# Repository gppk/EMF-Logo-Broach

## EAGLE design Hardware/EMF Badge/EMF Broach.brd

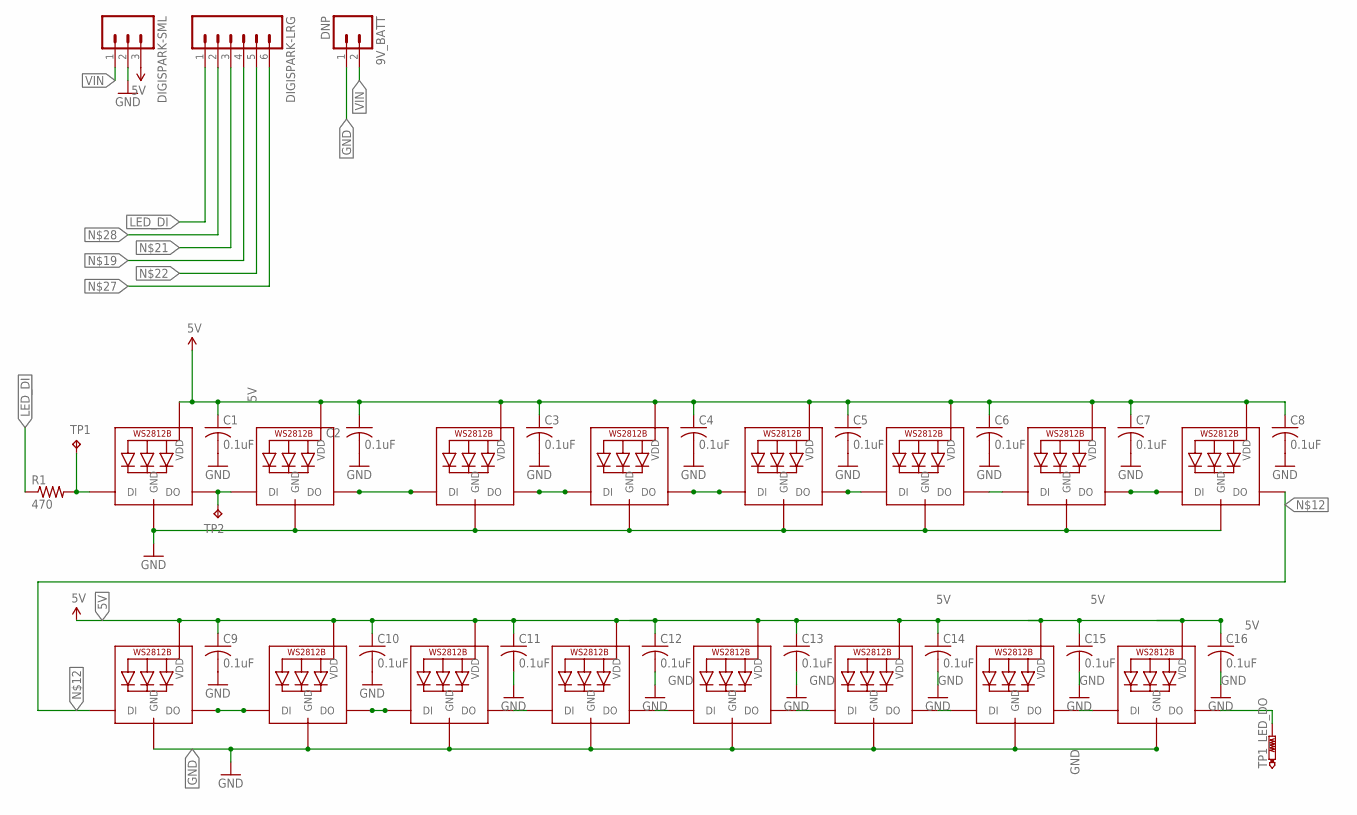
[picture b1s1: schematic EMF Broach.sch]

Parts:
9V_BATT: DNP; 02P
C1, C2, C3, C4, C5, C6, C7, C8, C9, C10, C11, C12, C13, C14, C15, C16: 0.1uF; C0603
DIGISPARK-LRG: M06SIP; 1X06
DIGISPARK-SML: M03PTH; 1X03
NEO_1, NEO_2, NEO_3, NEO_4, NEO_5, NEO_6, NEO_7, NEO_8, NEO_9, NEO_10, NEO_11, NEO_12, NEO_13, NEO_14, NEO_15, NEO_16: WS2812B5050; WS2812B
R1: 470; R0603
TP1, TP2: TPB1,27; B1,27
TP1_LED_DO: PTR1PAD1-17; P1-17

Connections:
5V: C1.1, C2.1, C3.1, C4.1, C5.1, C6.1, C7.1, C8.1, C9.1, C10.1, C11.1, C12.1, C13.1, C14.1, C15.1, C16.1, DIGISPARK-SML.3, NEO_1.1-VDD (VDD), NEO_2.1-VDD (VDD), NEO_3.1-VDD (VDD), NEO_4.1-VDD (VDD), NEO_5.1-VDD (VDD), NEO_6.1-VDD (VDD), NEO_7.1-VDD (VDD), NEO_8.1-VDD (VDD), NEO_9.1-VDD (VDD), NEO_10.1-VDD (VDD), NEO_11.1-VDD (VDD), NEO_12.1-VDD (VDD), NEO_13.1-VDD (VDD), NEO_14.1-VDD (VDD), NEO_15.1-VDD (VDD), NEO_16.1-VDD (VDD)
GND: 9V_BATT.1, C1.2, C2.2, C3.2, C4.2, C5.2, C6.2, C7.2, C8.2, C9.2, C10.2, C11.2, C12.2, C13.2, C14.2, C15.2, C16.2, DIGISPARK-SML.2, NEO_1.3-GND (GND), NEO_2.3-GND (GND), NEO_3.3-GND (GND), NEO_4.3-GND (GND), NEO_5.3-GND (GND), NEO_6.3-GND (GND), NEO_7.3-GND (GND), NEO_8.3-GND (GND), NEO_9.3-GND (GND), NEO_10.3-GND (GND), NEO_11.3-GND (GND), NEO_12.3-GND (GND), NEO_13.3-GND (GND), NEO_14.3-GND (GND), NEO_15.3-GND (GND), NEO_16.3-GND (GND)
LED_DI: DIGISPARK-LRG.1, R1.1
unnamed: NEO_1.2-DOUT (DO), NEO_2.4-DIN (DI), TP2.TP
unnamed: NEO_2.2-DOUT (DO), NEO_3.4-DIN (DI)
unnamed: NEO_10.2-DOUT (DO), NEO_11.4-DIN (DI)
unnamed: NEO_6.2-DOUT (DO), NEO_7.4-DIN (DI)
unnamed: NEO_7.2-DOUT (DO), NEO_8.4-DIN (DI)
unnamed: NEO_1.4-DIN (DI), R1.2, TP1.TP
unnamed: NEO_3.2-DOUT (DO), NEO_4.4-DIN (DI)
unnamed: NEO_4.2-DOUT (DO), NEO_5.4-DIN (DI)
unnamed: NEO_5.2-DOUT (DO), NEO_6.4-DIN (DI)
unnamed: NEO_8.2-DOUT (DO), NEO_9.4-DIN (DI)
unnamed: NEO_11.2-DOUT (DO), NEO_12.4-DIN (DI)
unnamed: NEO_9.2-DOUT (DO), NEO_10.4-DIN (DI)
unnamed: NEO_13.2-DOUT (DO), NEO_14.4-DIN (DI)
unnamed: NEO_15.2-DOUT (DO), NEO_16.4-DIN (DI)
unnamed: NEO_14.2-DOUT (DO), NEO_15.4-DIN (DI)
unnamed: NEO_12.2-DOUT (DO), NEO_13.4-DIN (DI)
unnamed: NEO_16.2-DOUT (DO), TP1_LED_DO.TP
VIN: 9V_BATT.2, DIGISPARK-SML.1

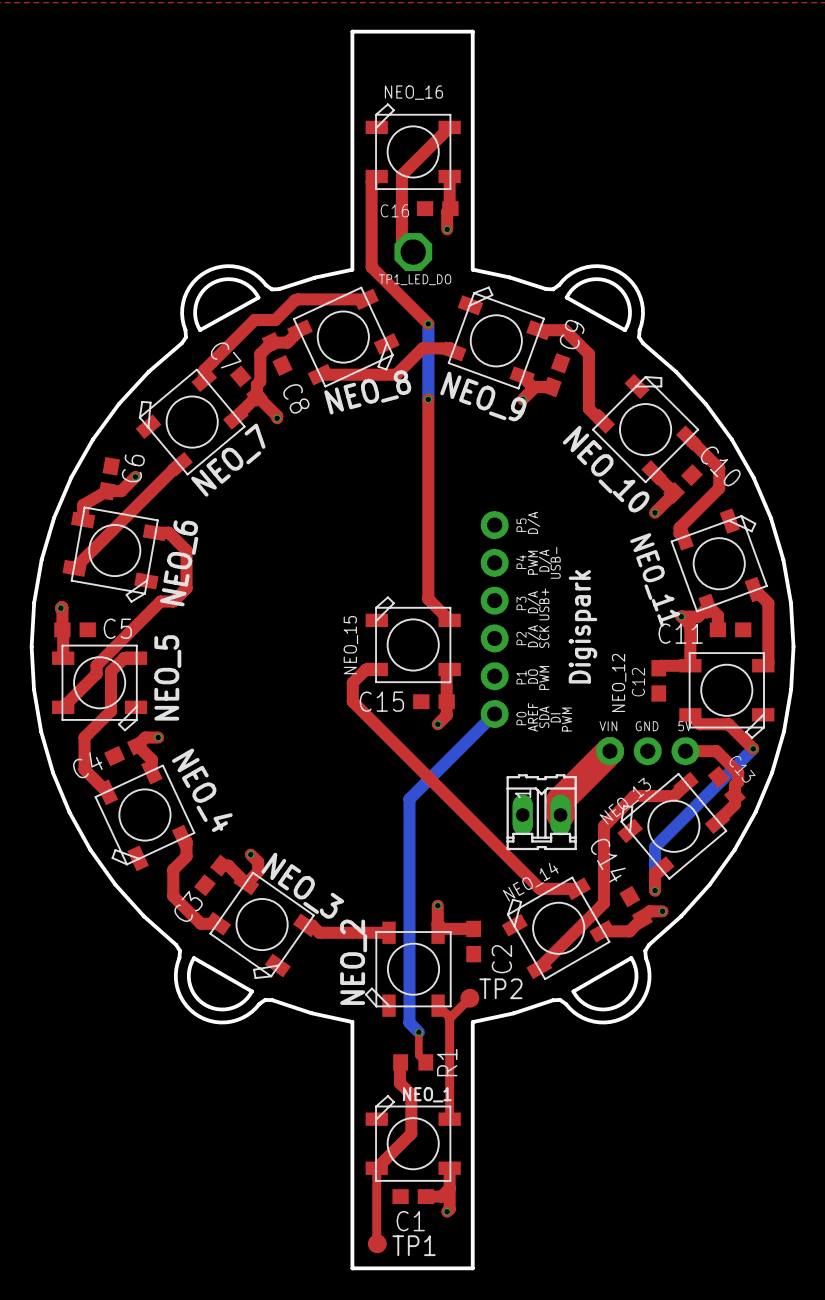
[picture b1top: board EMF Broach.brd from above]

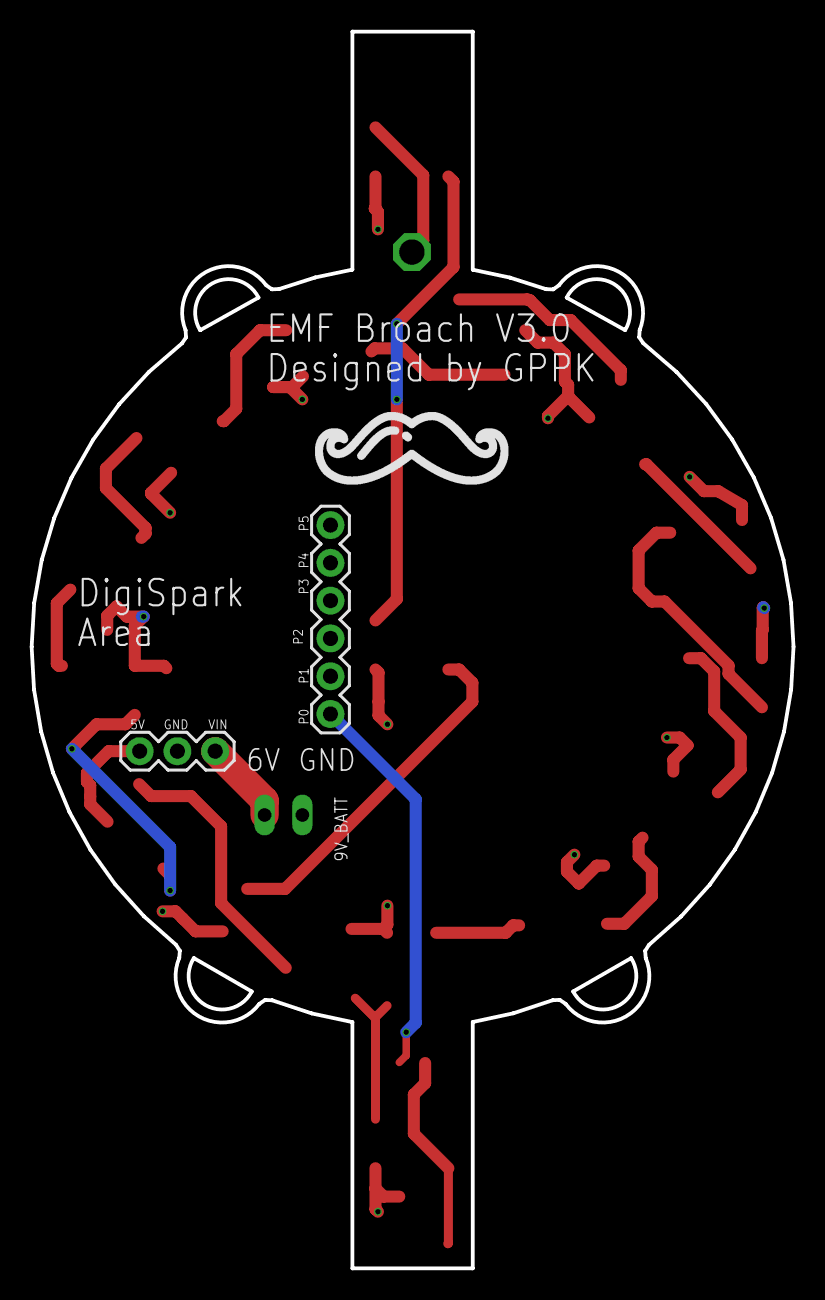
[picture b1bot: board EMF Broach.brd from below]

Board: 2 copper layers, 51.2 x 83.1 mm, 39 parts (2 on the bottom side), 21 nets.

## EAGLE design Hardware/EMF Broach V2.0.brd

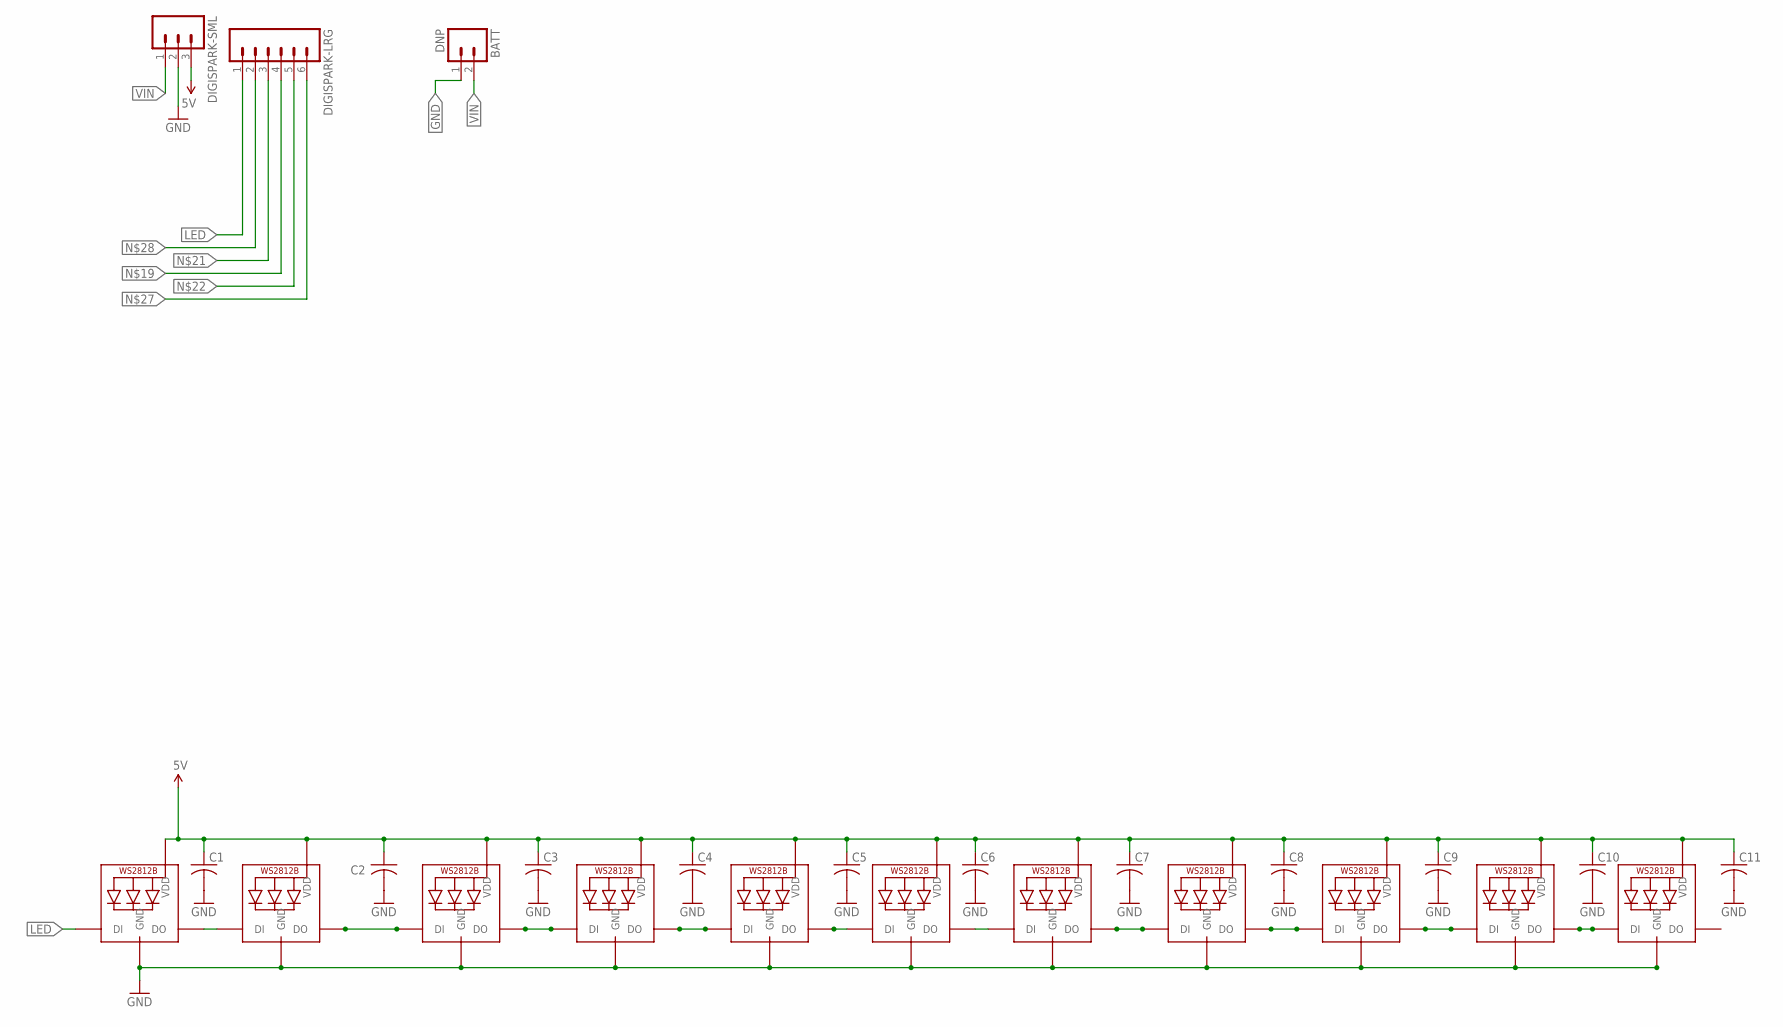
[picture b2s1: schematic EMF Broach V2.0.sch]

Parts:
BATT: DNP; 02P
C1, C2, C3, C4, C5, C6, C7, C8, C9, C10, C11: C-USC0603; C0603
DIGISPARK-LRG: M06SIP; 1X06
DIGISPARK-SML: M03PTH; 1X03
L1, L2, L3, L4, L5, L6, L7, L8, L9, L10, L11: WS2812B3535; LED3535

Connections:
5V: C1.1, C2.1, C3.1, C4.1, C5.1, C6.1, C7.1, C8.1, C9.1, C10.1, C11.1, DIGISPARK-SML.3, L1.1 (VDD), L2.1 (VDD), L3.1 (VDD), L4.1 (VDD), L5.1 (VDD), L6.1 (VDD), L7.1 (VDD), L8.1 (VDD), L9.1 (VDD), L10.1 (VDD), L11.1 (VDD)
GND: BATT.1, C1.2, C2.2, C3.2, C4.2, C5.2, C6.2, C7.2, C8.2, C9.2, C10.2, C11.2, DIGISPARK-SML.2, L1.3 (GND), L2.3 (GND), L3.3 (GND), L4.3 (GND), L5.3 (GND), L6.3 (GND), L7.3 (GND), L8.3 (GND), L9.3 (GND), L10.3 (GND), L11.3 (GND)
LED: DIGISPARK-LRG.1, L1.4 (DI)
unnamed: L1.2 (DO), L2.4 (DI)
unnamed: L2.2 (DO), L3.4 (DI)
unnamed: L10.2 (DO), L11.4 (DI)
unnamed: L6.2 (DO), L7.4 (DI)
unnamed: L7.2 (DO), L8.4 (DI)
unnamed: L3.2 (DO), L4.4 (DI)
unnamed: L4.2 (DO), L5.4 (DI)
unnamed: L5.2 (DO), L6.4 (DI)
unnamed: L8.2 (DO), L9.4 (DI)
unnamed: L9.2 (DO), L10.4 (DI)
VIN: BATT.2, DIGISPARK-SML.1

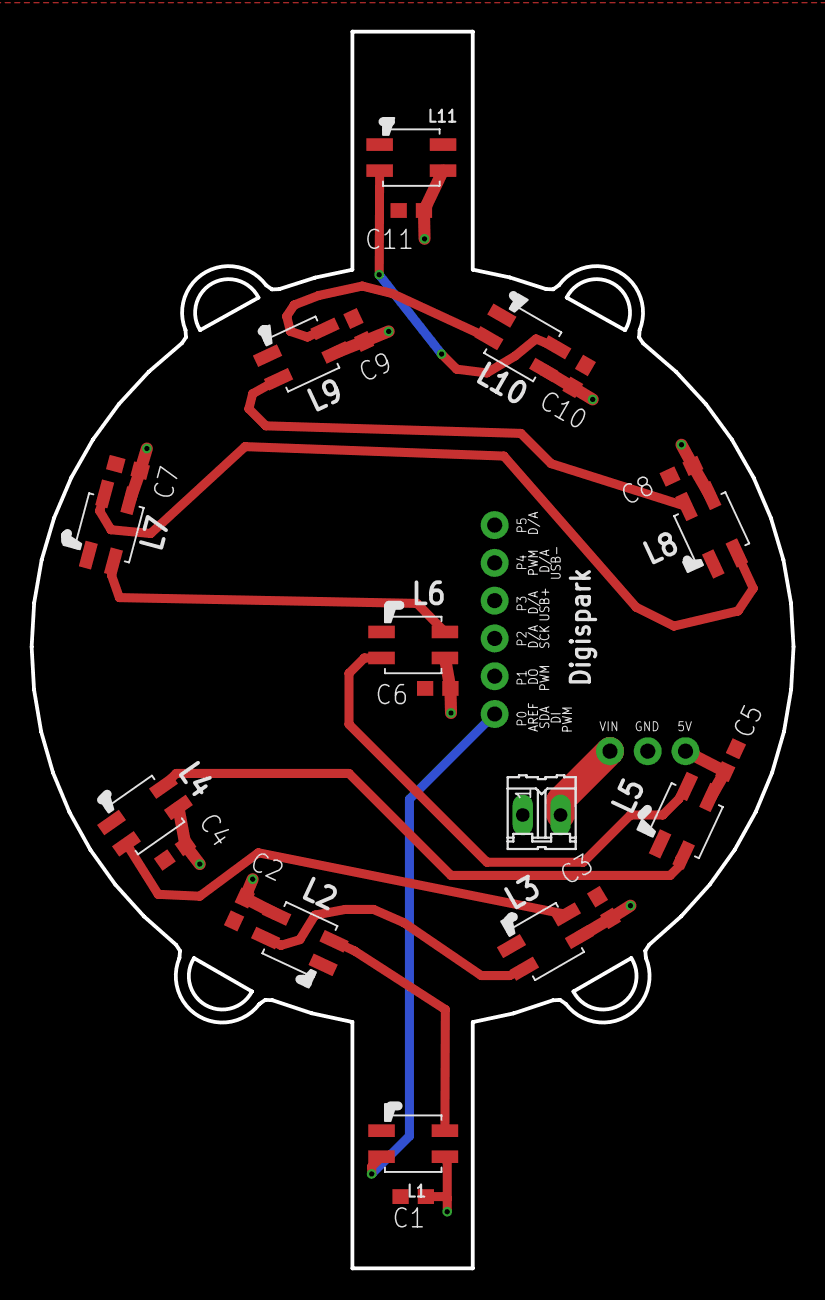
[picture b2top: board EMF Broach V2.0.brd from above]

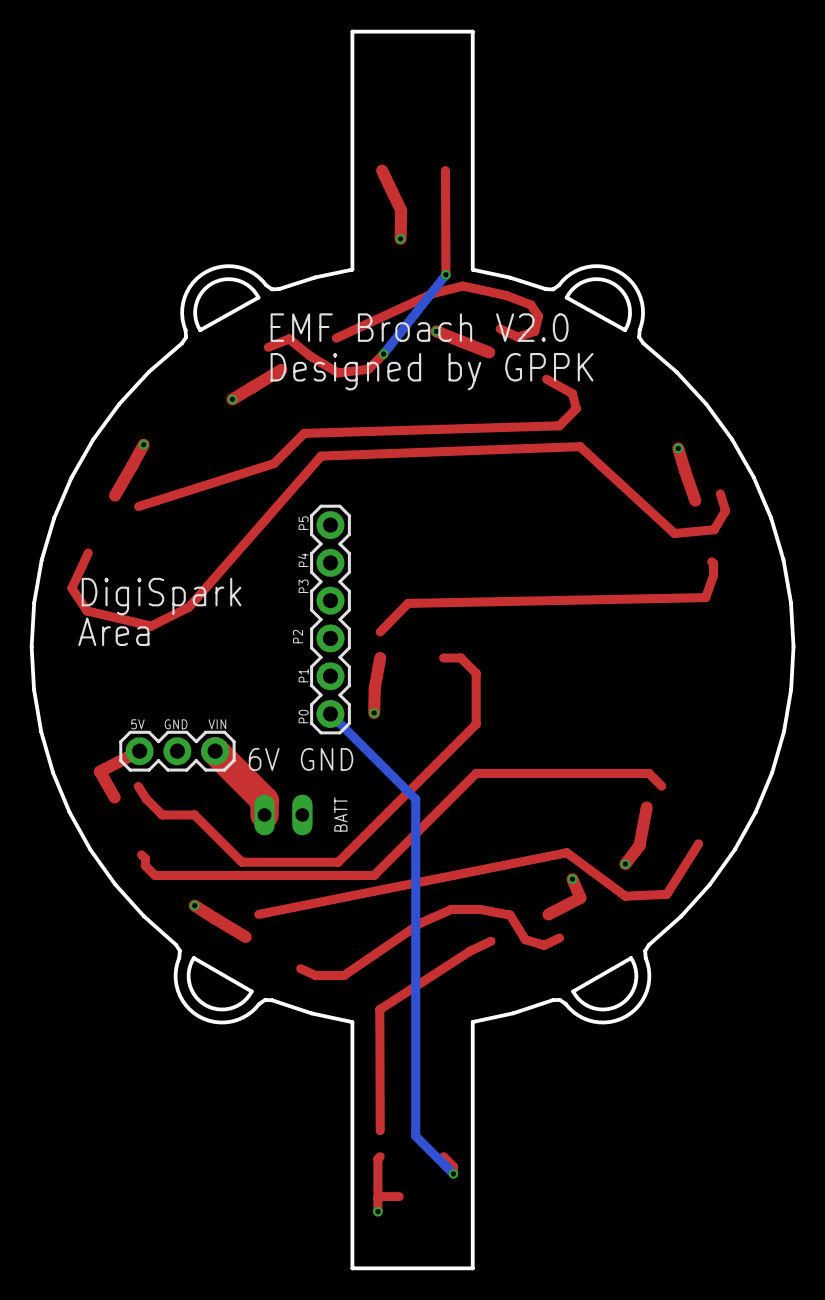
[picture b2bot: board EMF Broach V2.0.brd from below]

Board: 2 copper layers, 51.2 x 83.1 mm, 25 parts (2 on the bottom side), 14 nets.

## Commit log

2019-12-24 First Test Boards for manufacturing
    First set of boards to be manufactured for testing. Includes LEDs, wiring & Digispark connector. Will be used to test spacing of everything & that it actually works.
2020-01-16 Moved Hardware to specific folder
2020-01-16 First stab at software
    Generic arduino neopixel with flameflicker code.
2020-01-30 Mostly finished V2
    Moved battery holder terminal and rerouted all LEDs to correct datasheet
2022-04-12 Updated using reference design
    Old version didnt work. New version is very close to uploaded neopixel reference design.
    - More LEDs, tested on debug circuit.
    - Added 470 ohm resistor as per best practice
    - Needs routing.
2022-04-12 Routing complete
    Had to fix some nets on sch as well. GND/power that was overlayed but not conencted etc.
2022-04-13 fixed ERC/DRC
    fixed up the ERC/DRC. Haven't actually run on a board house one yet, probably mostly fine.
2022-04-13 Alexs Changes.
2022-04-14 Sent to fab
2022-05-11 Update EMF-Broach-Firmware.ino
    Final firmware that works well with the 9V battery and digispark. brightness can be upped to 150 and it works but 100 seems like a good compromise/
2022-05-11 Removal of legacy files
    a cleanup commit, removing some no longer useful files.
2022-05-11 Gerber files for V3.0 - Sent for manufacturing
    Manufactured gerber files. Sent to fab as V3.0 board run.
2022-05-11 Solder Stencil Files
    I have created a 3D printable solder stencil for this project using https://github.com/kirberich/gerber_to_scad
2022-05-11 Added printable PDFs
    schematic and pcb pdfs
2022-05-13 Create Diffuser Case.3mf
    Added diffuser case 3d printing files
2022-05-13 Kit & Media Files
    Added the Kit front page
    Added some media files

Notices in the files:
parts and their libraries:
SparkFun: Licensing: CC v3.0 Share-Alike You are welcome to use this library for commercial purposes.
